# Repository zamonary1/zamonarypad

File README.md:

# Zamonarypad

Zamonarypad is a low-latency capacitive touch 2-key keyboard. It is based on cheap ESP32-S2 microcontroller with native USB support.

Feel free to contact me via @zamonary1 via discord, i'll be happy to assist with any issues or questions you may have.

Code is licensed with BSD 3-Clause, PCB files are licensed with Creative Commons BY-SA 4.0. You can learn more in LICENSE

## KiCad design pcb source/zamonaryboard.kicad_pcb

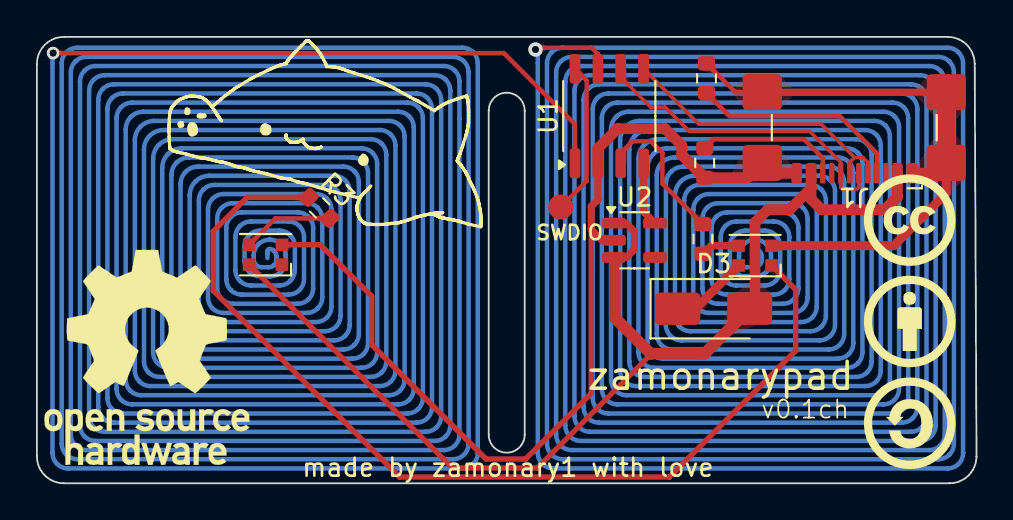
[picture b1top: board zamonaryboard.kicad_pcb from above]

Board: 2 copper layers, 52.2 x 24.8 mm, 10 parts (0 on the bottom side), 12 nets.

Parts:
D1, D2: WS2812B-2020; LED_WS2812B-2020_PLCC4_2.0x2.0mm
D3: US1B; D_SMA
J1: USB_C_Receptacle_USB2.0_14P; USB_C_Receptacle_GCT_USB4110
R1, R2: 5.1K; R_0603_1608Metric
R3, R6: 480; R_0603_1608Metric
U1: CH32V003JxMx; SOP-8_3.9x4.9mm_P1.27mm
U2: ME6211C33M5; SOT-23-5

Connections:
+3V3: U1.4 (VDD), U2.5 (V_{OUT})
D+: J1.A6 (D+), J1.B6 (D+), U1.6 (PC2)
D-: J1.A7 (D-), J1.B7 (D-), U1.5 (PC1)
GND: D1.2 (VSS), D2.2 (VSS), J1.A1 (GND), J1.A12 (GND), J1.B1 (GND), J1.B12 (GND), J1.S1 (SHIELD), R1.2, R2.1, U1.2 (VSS), U2.2 (V_{SS})
unnamed: D1.3 (DIN), R6.2
unnamed: D1.1 (DOUT), R3.1
unnamed: D1.4 (VDD), D3.1 (K)
unnamed: D2.3 (DIN), R3.2
unnamed: J1.A5 (CC1), R1.1
unnamed: J1.B5 (CC2), R2.2
VBUS: D2.4 (VDD), D3.2 (A), J1.A4 (VBUS), J1.A9 (VBUS), J1.B4 (VBUS), J1.B9 (VBUS), U2.1 (V_{IN}), U2.3 (CE)
aRGB_pin: R6.1, U1.3 (PA2)

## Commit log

2024-05-29 Initial commit, v0.1.1
2024-05-29 v0.1.1 fix
2024-05-29 initial images
2024-06-15 Added jlcpcb component annotations, small improvements
2024-07-01 big improvements to pcb
2024-07-01 exported gerber files for prototype 1.3, cleanup
2024-07-02 Many improvements to pcb and scheme, added testpoints for easier debugging
2024-07-04 improved routing, fixes
2024-07-04 Improvements on pcb, more components, better routing and better labling.
2024-07-27 small improvements, cleanup
2024-07-28 lower latency because of switch from interrupts to directly reading the touch values
2024-08-16 firmware improvements
2024-08-16 putting built executables of desktop app to dedicated dir, corresponding Makefile and .gitignore changes
2024-08-17 Python desktop app improvements, PCB pre-v1
2024-08-20 v1 commit, desktop app improvements
2024-08-20 cleanup, license, readme update
2024-08-22 cleanup
2024-08-26 BIG improvements to firmware, 200 times more efficient now, had to artificially lower the poll rate to 1000hz for buttons to function properly
2024-08-27 desktop app improvements, now uses gramms of force to use as sensitivity measure
2024-09-08 improvements
2024-09-10 Flipped type-c port and main buttons to the back side, changed reset/boot button to be slimmer, initial new branch commit
2024-09-20 WS2812 2020 on the pcb! Not necesseary for proper work
2024-09-20 image update
2024-10-01 v1.2-f, added WS2812-2020 argb leds on the backside of the board (unnecesseary), improvements to pcb routing
2024-10-17 Added a cut between sensitive pads to give some tactile feedback to the board.
2024-12-22 Firmware code cleanup, add support for addressible LEDs.
2025-01-01 Firmware code cleanup and support of changing color of start animation and click indication.
2025-01-01 Move to Platformio ide
2025-01-05 Restructurization of firmware
2025-01-06 Added auto-build github workflow, code cleanup
2025-01-11 Testing of auto-release of firmware
2025-01-11 platformio.yml action update
2025-02-01 Moved firmware to submodule
2025-02-01 Git submodule update
2025-02-01 submodule update
2025-02-01 .gitignore update
2025-02-01 firmware module
2025-02-01 firmware as submodule
2025-02-01 Remove actions, moved to firmware submodule
2025-02-01 Working pcb
